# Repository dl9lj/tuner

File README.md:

# tuner
wireless remote control for different antenna tuners

Yaesu FC-1000 / FC-800
started with buying a Yaesu Automatic Antenna Tuner FC-1000 w/o control unit. I started with removing the existing controller and thought about to do a replacement with an atmega328p in combination with 3 HC595 shift register. Interface to a laptop pc via uart. I had this setup running (328p firmware in C). But after working with NRF24L01 modules I decided to do the interface wireless. 328p is no longer required but the 595 board can be used.The 3 HC595 are connected via wires and DSUB9 connector to an externel arduino with NRF24L01 module. I wrote a python script with slider and radio buttons. Best band settings were programmed to radio buttons of the script. Later I found out, that my FT-840 has a controller included and I only need to have a cable... But the new setup is more flexible and can be used with any transceiver. 

LDG AT-1000 (2003)
is a asymmetric low-pass 1kW antenna tuner with manual control. Automatic does not really work well and the tuner had some issues with internal EMC. But in general it has good L and C components an uses an Allegro UCN5832 to control the 15 relays. Allegro UCN5832 has an 3-wire interface similar to SPI (data, clock, strobe). Some housings have a hole for D-SUB9 connector, but I have not found an controller option. I have have removed the connection between MC68HC11 and UCN5832 (chokes L11, L12 and L13) and connected UCN5832 with wires to a DSUB9 connector (data, clock, strobe, gnd, 12V). 

Christian Koppler (DL3LAC)
is a symmetric antenna coupler. The main unit contains only L, C and relays and will be controlled with a control unit via a 25-wire cable (16 pins for relays, 7 pins for 12V, 2 pins spare). I have created an interface board with TI TPIC6B595 driver 2s (2p for inductor relays) and 5V Supply. A arduino uno with NRF24L01 will be connected to this interface for receiving control data from the NRF24L01 transmitter.

The NRF24L01 transmitter will be the same for all 3 antenna tuners. NRF24L01 receiver hardware is equal for Yaesu and Christian Koppler. LDG needs a Strobe signal from pin 3 of the arduino. It is not required to build up 3 receiver but a dedicated receiver for each tuner helps to keep the overview. Each receiver requires a separate arduino firmware. 

Software is written very straight forward (no error correction / udp style). GUI does not show the real state after start (only after pushing the button). After start you have to press the "AllOff" button to set everything to zero/off.Terminal shows the output sequence. 

Additional interface hardware is required for Yaesu and Christian Koppler. The schematics for the Yaesu tuner has an wrong order for the relays connected to pin 12 to 19 (RL11,10,9,8,7,6,5,1_2 would be better). Later I have fixed that mistake with jumper wires. In between I have used a python script with LUT to do the correction  but correction in hardware makes programming easier. U1 of the Christian Koppler interface needs a 2nd TPIC6B595 on top (all pins connected except pin18 (nc)) because current output of a single chip is too weak for driving 4 relays in parallel. The board of the LDG Tuner has already the Allegro UCN5832 shift-register which can directly connected to the external arduino. Please check wiring.txt file for connections (is more recent than the existing schematics).

#### GUI
- simple GUI with wxPython
- start with "AllOff" and set all buttons to 0
- output data will be printed on the terminal window

#### Christian Koppler with remote receiver (Arduino with NRF24L01 module)
- this euro box can be put with some rain protection in the backyard to connect the antenna
- 12V from VRLA battery will be used

#### Interface inside the housing
- tuner pcb has a male DSUB25 connector

#### Interface board for Christian Koppler
- with 5V supply fot TPIC6B595 components
- 2nd TPIC6B595 is soldered on top of U1 (pin 18 not connected)

#### LDG AT-1000 Tuner
- front view

#### LDG AT-1000 Tuner
- rear view with added DSUB9 female

#### LDG AT-1000 Tuner
- top view
- see wiring to connect Allegro UCN5832

#### LDG AT-1000 Tuner
- small pcb with chokes to connect Allegro UCN5832

#### LDG AT-1000 Tuner
- wiring / connection

#### Receiver box
- Arduino Uno with NRF24L01 module
- Yaesu and Christian Koppler can use the same hardware (Arduino pins 4,5,6) but need different code
- LDG uses Arduino pins 3,4,5

#### Receiver and transmitter boxes 
- looking very similar

#### Transmitter box
- has USB connector for the connection to a laptop pc
- can also act w/o pc (currently only for testing) 

#### Yaesu FC-1000 Antenna Tuner
- top view
- housing can withstand some raindrops

#### Yaesu FC-1000 Antenna Tuner
- nice device - 40pin controller were replaced with a small pcp (3 x HC595)
- 3 sections can nearly tune and match any antenna (up to 150W)

#### Yaesu FC-1000 interface board
- see wiring

#### Yaesu FC-1000 interface board
- error was corrected with jumper wires

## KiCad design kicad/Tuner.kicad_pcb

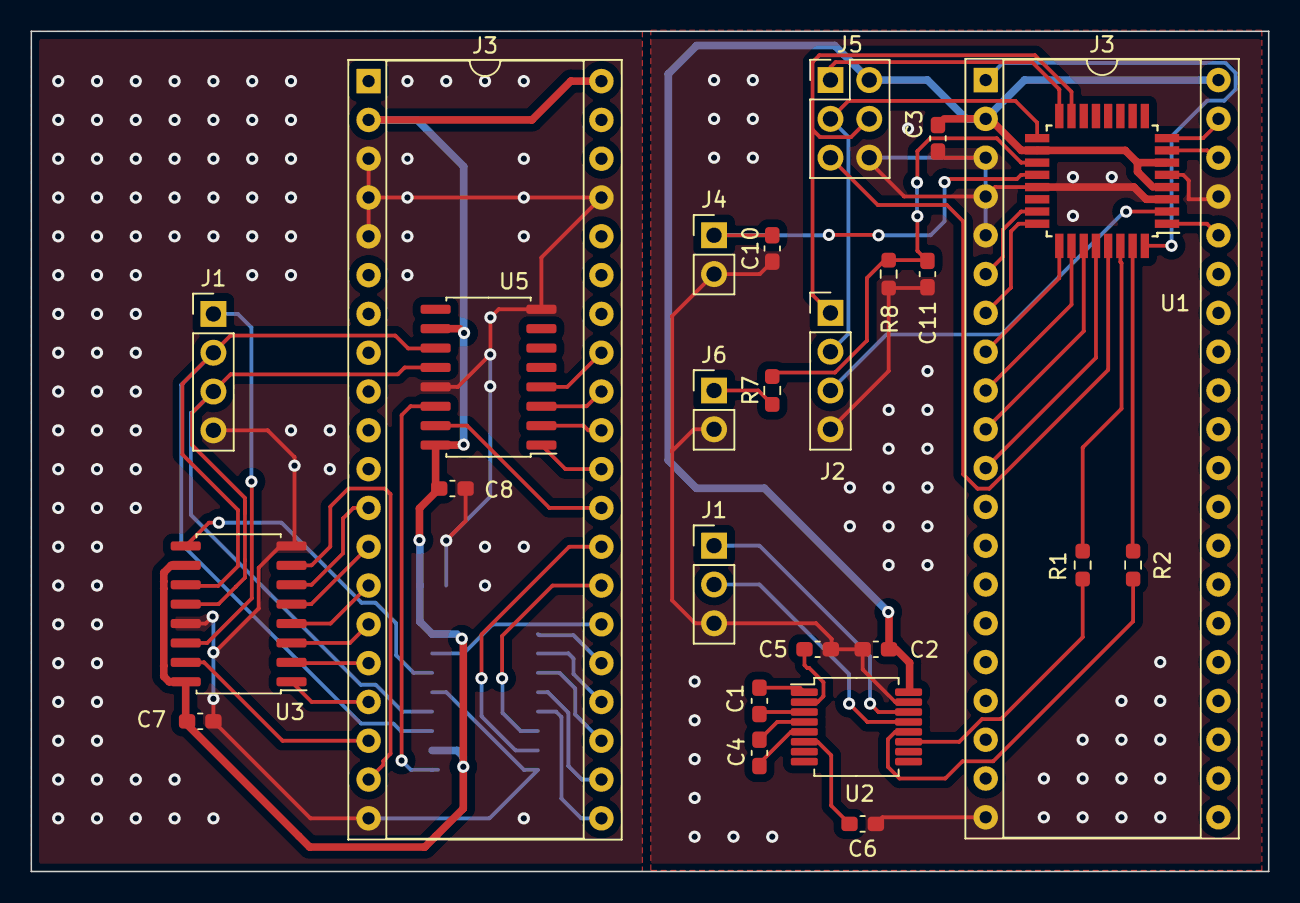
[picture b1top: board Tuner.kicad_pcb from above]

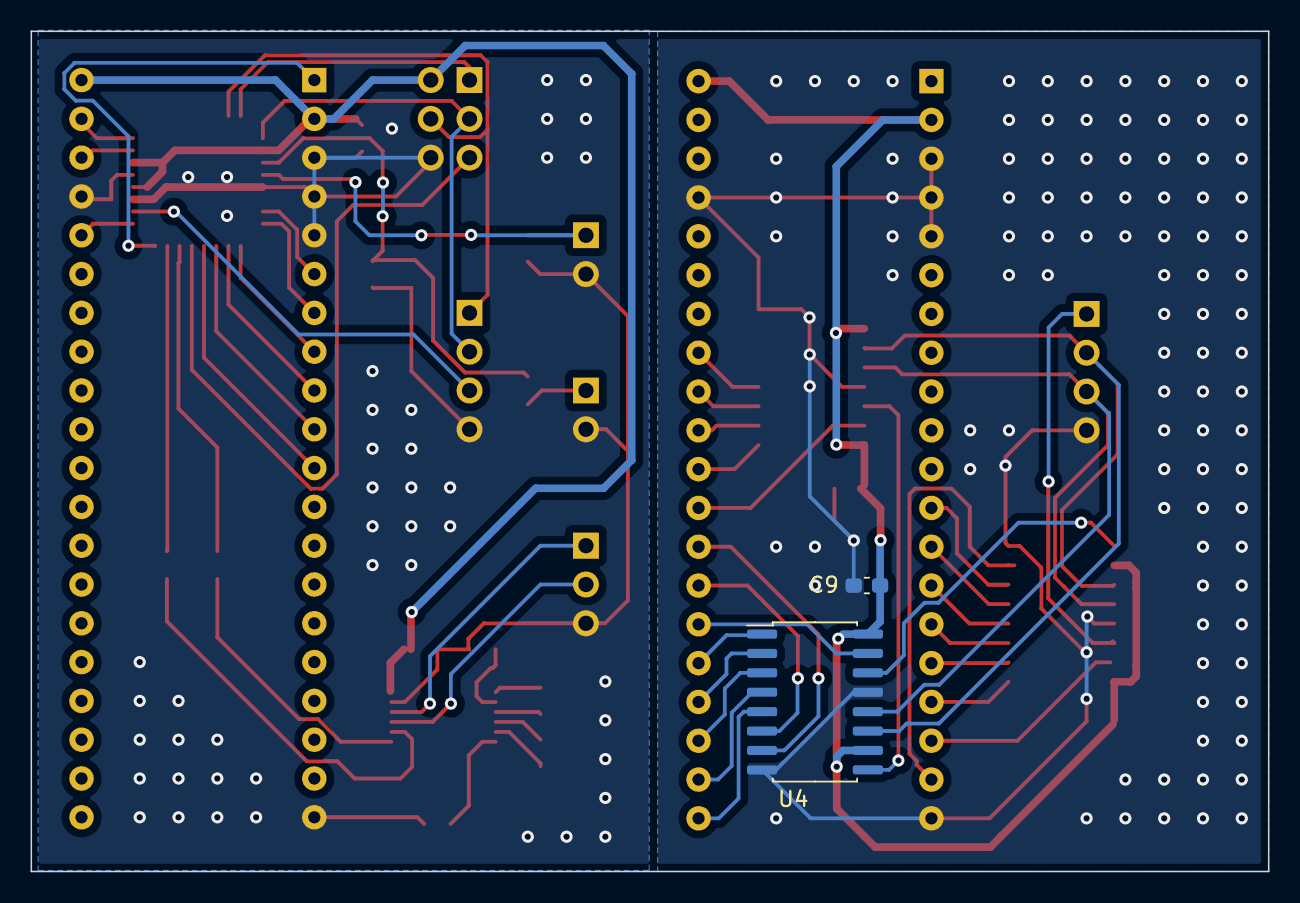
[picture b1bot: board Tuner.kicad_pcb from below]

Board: 2 copper layers, 81.0 x 55.0 mm, 28 parts (2 on the bottom side), 28 nets.

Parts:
C1, C2, C3, C4, C5, C6, C7, C8, C9, C10, C11: 100n; C_0603_1608Metric_Pad1.08x0.95mm_HandSolder
J1: 3pin; PinHeader_1x03_P2.54mm_Vertical
J1#2, J2: 4pin; PinHeader_1x04_P2.54mm_Vertical
J3, J3#2: 40pin; DIP-40_W15.24mm_Socket
J4, J6: 2pin; PinHeader_1x02_P2.54mm_Vertical
J5: 2x3pin; PinHeader_2x03_P2.54mm_Vertical
R1, R2, R7, R8: 10k; R_0603_1608Metric_Pad0.98x0.95mm_HandSolder
U1: ATmega328PB-A; TQFP-32_7x7mm_P0.8mm
U2: MAX232; SSOP-16_5.3x6.2mm_P0.65mm
U3, U4, U5: 74HC595; SO-16_5.3x10.2mm_P1.27mm

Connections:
+5V: C2.2, C3.1, C7.1, C8.1, C9.1, J3.2, J3.40, J3#2.2, J3#2.40, J5.2, U1.4 (VCC), U1.6 (PE1), U1.18 (AVCC), U2.16 (VCC), U3.10 (~SRCLR), U3.16 (VCC), U4.10 (~SRCLR), U4.16 (VCC), U5.10 (~SRCLR), U5.16 (VCC)
GND: C2.1, C3.2, C5.2, C6.2, C7.2, C8.2, C9.2, C10.1, C11.2, J1.3, J1#2.4, J2.4, J3.3, J3.4, J3.5, J3.20, J3.37, J3#2.3, J3#2.4, J3#2.5, J3#2.20, J3#2.37, J4.2, J5.6, J6.2, R8.1, U1.3 (PE0), U1.5 (GND), U1.21 (GND), U2.15 (GND), U3.8 (GND), U3.13 (~OE), U4.8 (GND), U4.13 (~OE), U5.8 (GND), U5.13 (~OE)
LATCH: J1#2.3, J2.3, U1.2 (PD4), U3.12 (RCLK), U4.12 (RCLK), U5.12 (RCLK)
MOSI: J1#2.1, J2.1, J5.4, U1.15 (PB3), U3.14 (SER)
unnamed: U3.9 (QH'), U4.14 (SER)
unnamed: U4.9 (QH'), U5.14 (SER)
RL1_2: J3#2.19, U3.7 (QH)
RL3: J3#2.28, U4.7 (QH)
RL4: J3#2.27, U4.6 (QG)
RL5: J3#2.18, U3.15 (QA)
RL6: J3#2.17, U3.1 (QB)
RL7: J3#2.16, U3.2 (QC)
RL8: J3#2.15, U3.3 (QD)
RL9: J3#2.14, U3.4 (QE)
RL10: J3#2.13, U3.5 (QF)
RL11: J3#2.12, U3.6 (QG)
RL12: J3#2.26, U4.15 (QA)
RL13: J3#2.25, U4.1 (QB)
RL14: J3#2.24, U4.2 (QC)
RL15: J3#2.23, U4.3 (QD)
RL16: J3#2.22, U4.4 (QE)
RL17: J3#2.21, U4.5 (QF)
RL18: J3#2.29, U5.15 (QA)
RL19: J3#2.30, U5.1 (QB)
RL20: J3#2.31, U5.2 (QC)
RL21: J3#2.32, U5.3 (QD)
RL22: J3#2.33, U5.4 (QE)
SCLK: J1#2.2, J2.2, J5.3, U1.17 (PB5), U3.11 (SRCLK), U4.11 (SRCLK), U5.11 (SRCLK)

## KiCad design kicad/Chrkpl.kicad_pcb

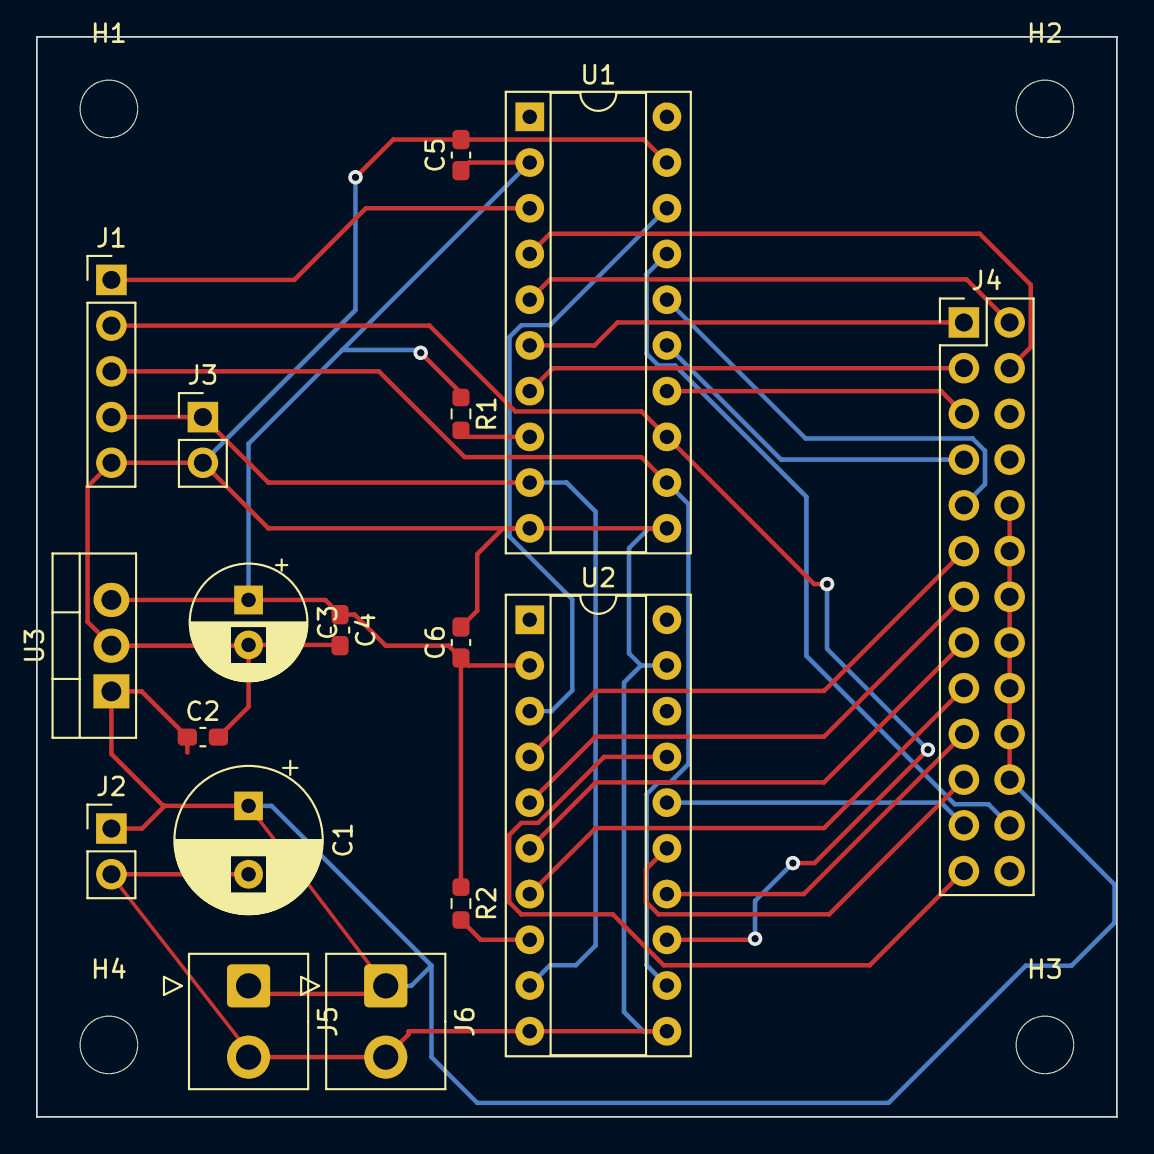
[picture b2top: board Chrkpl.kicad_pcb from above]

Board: 2 copper layers, 60.0 x 60.0 mm, 21 parts (0 on the bottom side), 26 nets.

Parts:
C1: 100u; CP_Radial_D8.0mm_P3.80mm
C2, C4, C5, C6: 100n; C_0603_1608Metric_Pad1.08x0.95mm_HandSolder
C3: 10u; CP_Radial_D6.3mm_P2.50mm
H1, H2, H3, H4: MH; MountingHole_3.2mm_M3
J1: 5pin; PinHeader_1x05_P2.54mm_Vertical
J2, J3: 2pin; PinHeader_1x02_P2.54mm_Vertical
J4: 26pin; PinHeader_2x13_P2.54mm_Vertical
J5, J6: 2pin; TE_826576-2_1x02_P3.96mm_Vertical
R1, R2: 10k; R_0603_1608Metric_Pad0.98x0.95mm_HandSolder
U1, U2: TPIC6595; DIP-20_W7.62mm_Socket
U3: L7805; TO-220-3_Vertical

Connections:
+5V: C3.1, C4.1, C5.1, C6.1, R1.1, R2.1, U1.2 (VCC), U2.2 (VCC), U3.3 (OUT)
+12V: C1.1, C2.1, J2.1, J4.10, J4.12, J4.14, J4.16, J4.18, J4.20, J4.22, J5.1, J6.1, U3.1 (IN)
C1: J4.11, U2.4 (DRAIN0)
C2: J4.13, U2.5 (DRAIN1)
C3: J4.15, U2.6 (DRAIN2)
C4: J4.17, U2.7 (DRAIN3)
C5: J4.19, U2.14 (DRAIN4)
C6: J4.21, U2.15 (DRAIN5)
C7: J4.23, U2.16 (DRAIN6)
C8: J4.25, U2.17 (DRAIN7)
GND: C1.2, C2.2, C3.2, C4.2, C5.2, C6.2, J1.5, J2.2, J3.2, J5.2, J6.2, U1.10 (PGND), U1.11 (PGND), U1.19 (LGND), U2.10 (PGND), U2.11 (PGND), U2.19 (LGND), U3.2 (GND)
HTP: J4.24, U1.17 (DRAIN7)
L1: J4.4, U1.4 (DRAIN0)
L2: J4.2, U1.5 (DRAIN1)
L3: J4.1, U1.6 (DRAIN2)
L4: J4.3, U1.7 (DRAIN3)
L5: J4.5, U1.14 (DRAIN4)
L6: J4.7, U1.15 (DRAIN5)
L7: J4.9, U1.16 (DRAIN6)
unnamed: J1.1, U1.3 (SER_IN)
unnamed: J1.2, U1.13 (SRCK), U2.13 (SRCK)
unnamed: J1.3, U1.12 (RCLK), U2.12 (RCLK)
unnamed: J1.4, J3.1, U1.9 (~G), U2.9 (~G)
unnamed: U1.18 (SER_OUT), U2.3 (SER_IN)
unnamed: R1.2, U1.8 (~SRCLR)
unnamed: R2.2, U2.8 (~SRCLR)
